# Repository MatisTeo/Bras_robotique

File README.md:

# 🤖 Projet Bras Robotique Contrôlé par Gant Connecté

## 🎥 Démonstration vidéo

## 📘 Présentation

Ce projet consiste à développer un **bras robotique à faible coût**, capable d'exécuter :
- des **mouvements automatiques prédéfinis**
- un **contrôle manuel à distance** à l'aide d’un **gant connecté**

L'objectif est de démontrer une alternative simple et économique pour la télémanipulation dans des environnements industriels.

## 🧠 Membres du projet
- **Téo Baillot d’Estivaux** — responsable software, modélisation 3D, banc de test
- **Matis Jaquet** — responsable hardware, PCB, assemblage électronique

## 🔧 Fonctionnalités
- Contrôle **automatique** via séquences programmées
- Contrôle **manuel en temps réel** via un gant avec capteur flex + MPU-6050
- Communication **sans fil via ESP-NOW (Wi-Fi)** entre gant et bras
- Structure imprimée en 3D, légère et modulaire
- Retour d’effort par détection de courant via INA219

## 📂 Contenu du dépôt
- `Hardware/` : Schémas et PCB sous KiCad
- `Software/` : Codes Arduino pour l’émetteur (gant) et le récepteur (bras)
- `Photos/Spécification/` : Images du montage
- `Memoire_Baillot_Jaquet.pdf` : Mémoire complet du projet (ELEC4 FISA 2024/2025)

## 🛠️ Composants utilisés
- 2x ESP32
- 1x MPU-6050 (accéléromètre)
- 1x capteur flex
- 5x servomoteurs SG90
- 1x INA219
- 1x bouton poussoir
- Câblage, breadboards, batteries

## 🚀 Instructions de montage
1. Imprimer les pièces 3D du bras
2. Souder les composants sur les PCB fournis
3. Assembler le gant en cousant les composants selon le schéma
4. Flasher les codes sur les ESP32 avec Arduino IDE
5. Alimenter les deux systèmes et tester les modes automatique et manuel

## 📎 Liens utiles
- [🔗 Dépôt GitHub](https://github.com/MatisTeo/Bras_robotique)
- [📄 Mémoire complet (PDF)](./Divers/Memoire_Baillot_Jaquet.pdf)

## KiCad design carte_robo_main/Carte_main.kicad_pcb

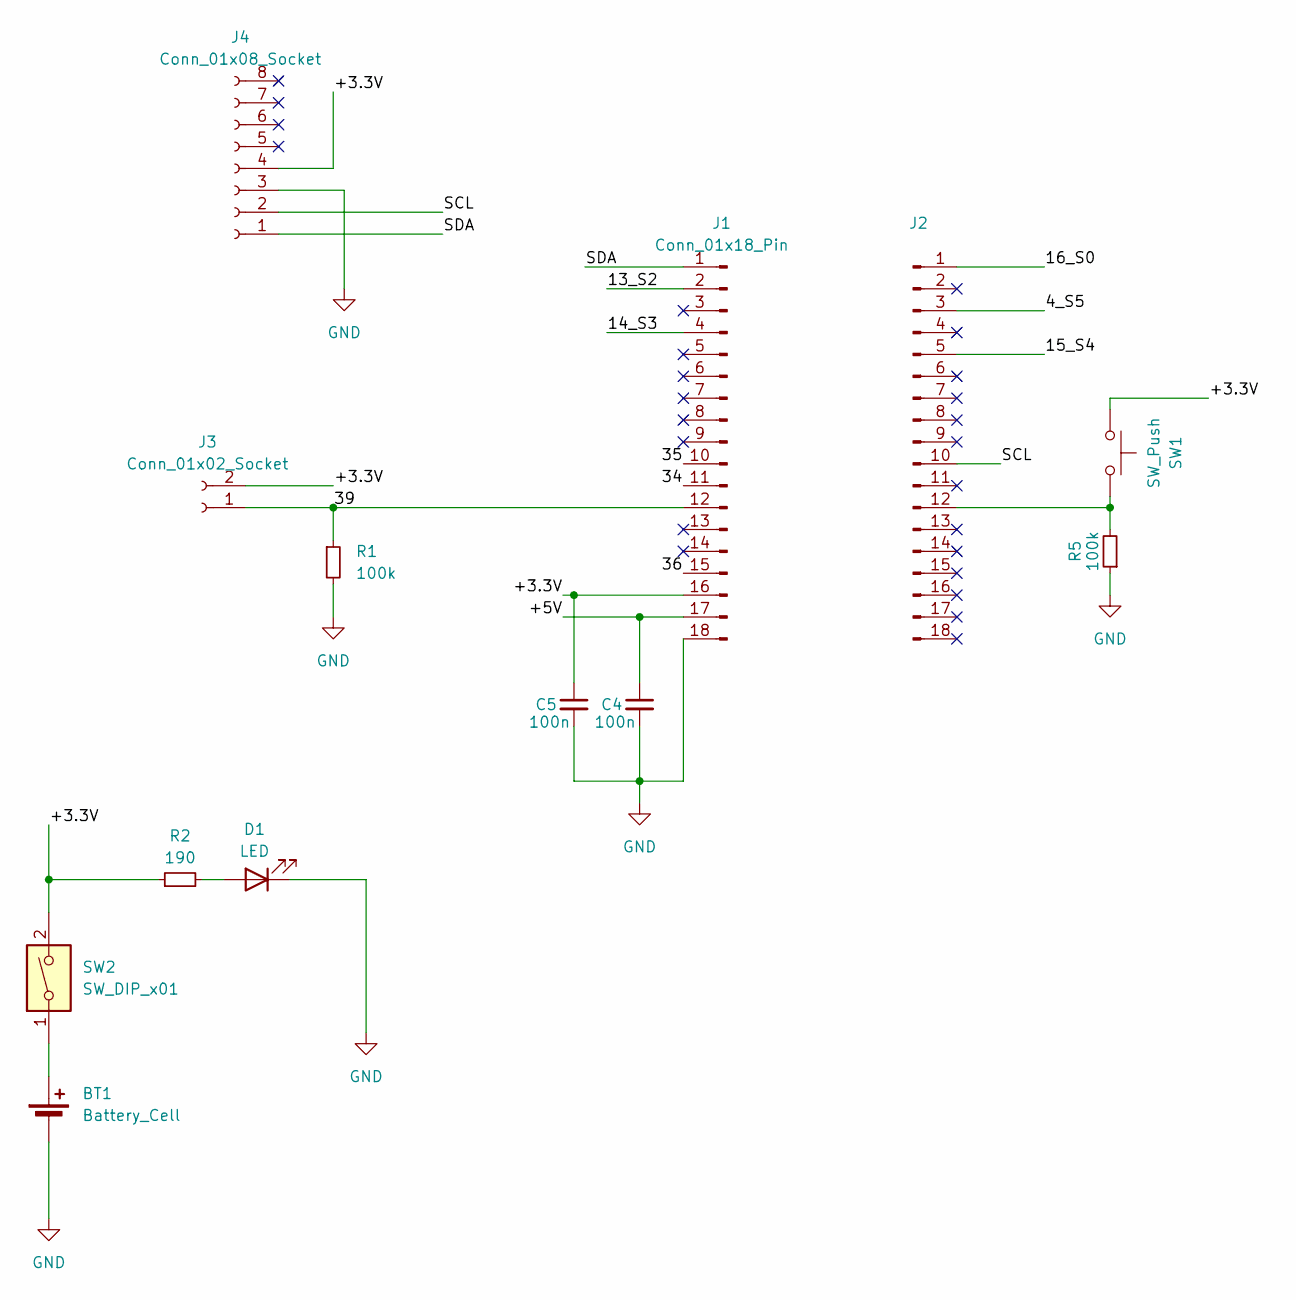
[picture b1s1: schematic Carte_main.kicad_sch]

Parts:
BT1: Battery_Cell; PinHeader_1x02_P2.54mm_Vertical
C4, C5: 100n; C_Disc_D4.3mm_W1.9mm_P5.00mm
D1: LED; LED_D3.0mm
J1, J2: Conn_01x18_Pin; PinHeader_1x18_P2.54mm_Vertical
J3: Conn_01x02_Socket; PinHeader_1x02_P2.54mm_Vertical
J4: Conn_01x08_Socket; PinHeader_1x08_P2.54mm_Vertical
R1, R5: 100k; R_Axial_DIN0207_L6.3mm_D2.5mm_P10.16mm_Horizontal
R2: 190; R_Axial_DIN0207_L6.3mm_D2.5mm_P10.16mm_Horizontal
SW1: SW_Push; SW_PUSH_6mm_H5mm
SW2: SW_DIP_x01; SW_slide-03_P5_THT

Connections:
/4_S5: J2.3
/13_S2: J1.2
/14_S3: J1.4
/15_S4: J2.5
/16_S0: J2.1
/34: J1.11
/35: J1.10
/36: J1.15
/39: J1.12, J3.1, R1.1
/+3.3V: C5.1, J1.16, J3.2, J4.4, R2.1, SW1.1, SW2.2
/+5V: C4.1, J1.17
/SCL: J2.10, J4.2
/SDA: J1.1, J4.1
GND: BT1.2 (-), C4.2, C5.2, D1.1 (K), J1.18, J4.3, R1.2, R5.1
unnamed: BT1.1 (+), SW2.1
unnamed: D1.2 (A), R2.2
unnamed: J2.12, R5.2, SW1.2

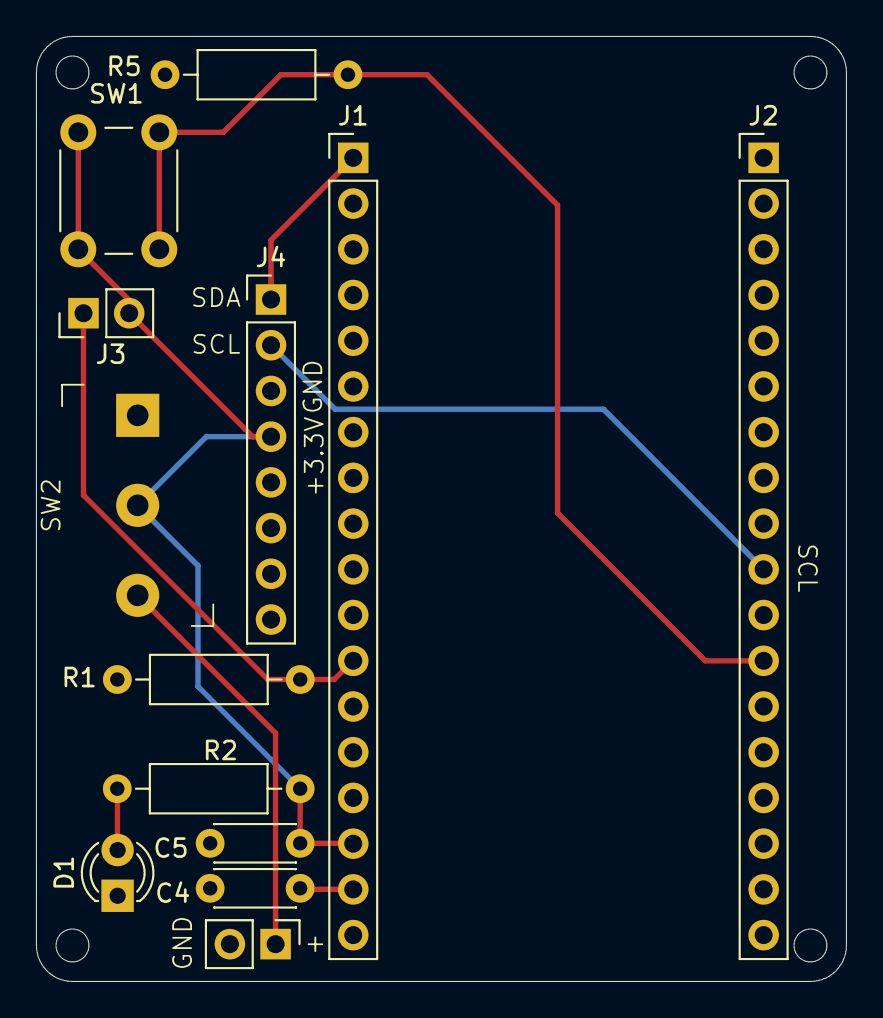
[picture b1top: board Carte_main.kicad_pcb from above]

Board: 2 copper layers, 45.0 x 52.5 mm, 13 parts (0 on the bottom side), 9 nets.

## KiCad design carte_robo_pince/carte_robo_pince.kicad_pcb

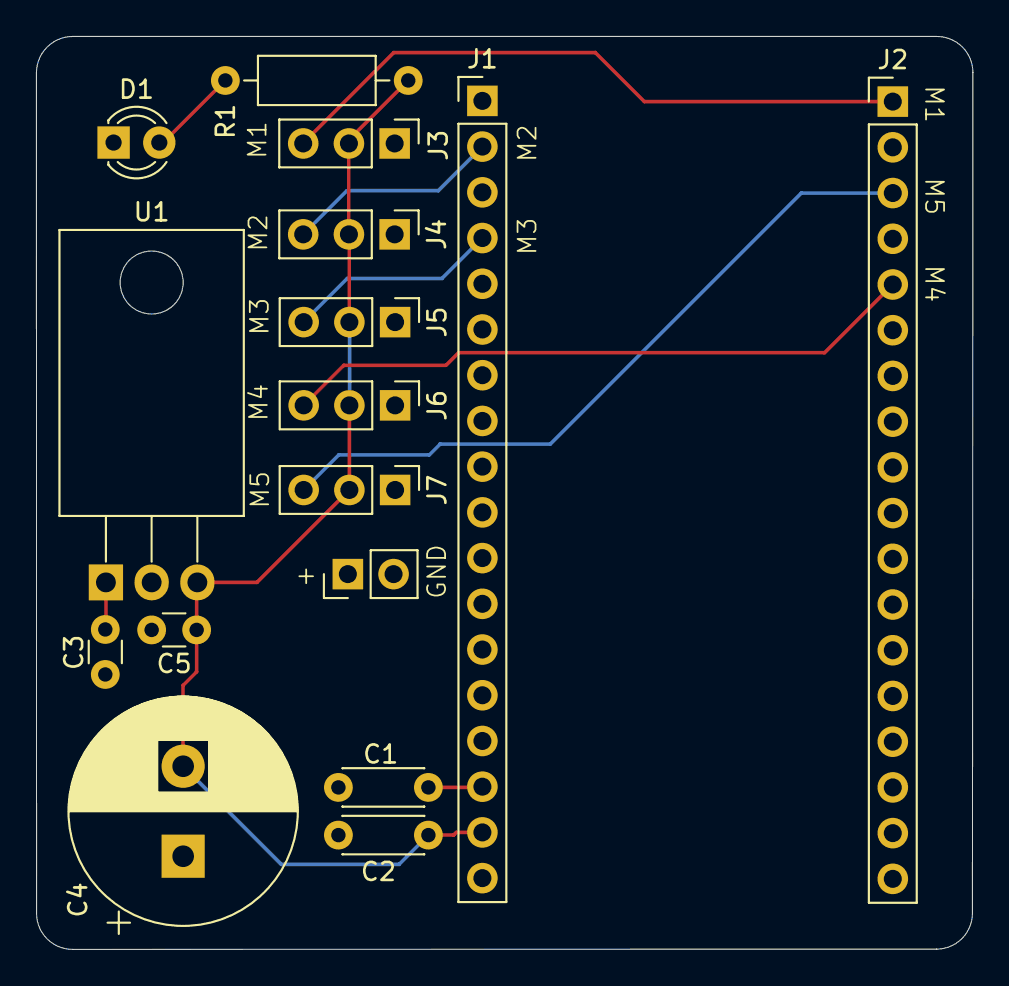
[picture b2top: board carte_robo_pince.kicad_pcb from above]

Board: 2 copper layers, 52.0 x 50.7 mm, 16 parts (0 on the bottom side), 10 nets.

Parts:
BT1: +8V; PinHeader_1x02_P2.54mm_Vertical
C1, C2: 100n; C_Disc_D4.3mm_W1.9mm_P5.00mm
C3: 0.33pF; C_Disc_D3.0mm_W1.6mm_P2.50mm
C4: 1000u; CP_Radial_D12.5mm_P5.00mm
C5: 0.1uF; C_Disc_D3.0mm_W1.6mm_P2.50mm
D1: LED; LED_D3.0mm
J1, J2: Conn_01x18_Pin; PinHeader_1x18_P2.54mm_Vertical
J3, J4, J5, J6, J7: Conn_01x03_Socket; PinHeader_1x03_P2.54mm_Vertical
R1: 330; R_Axial_DIN0207_L6.3mm_D2.5mm_P10.16mm_Horizontal
U1: KA78M05_TO252; TO-220-3_Horizontal_TabDown

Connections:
/4_S5: J2.3, J7.3
/13_S2: J1.2, J4.3
/14_S3: J1.4, J5.3
/15_S4: J2.5, J6.3
/16_S0: J2.1, J3.3
/+3.3V: C1.1, J1.16
/+5V: C2.1, C4.2, C5.1, J1.17, J3.2, J4.2, J5.2, J6.2, J7.2, R1.2, U1.3 (VO)
GND: BT1.2 (-), C1.2, C2.2, C3.2, C4.1, C5.2, D1.1 (K), J1.18, J3.1, J4.1, J5.1, J6.1, J7.1, U1.2 (GND)
unnamed: D1.2 (A), R1.1
unnamed: C3.1, U1.1 (VI)

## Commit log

2024-09-23 docs ajoutée
2024-11-28 compte rendu crée
2024-12-09 les deux rop merge
2024-12-14 14/12/2024
2025-01-07 pcb done
2025-02-06 last update
2025-03-02 version
2025-03-19 19/03
2025-04-01 01/04/25
2025-05-05 before copy branche matis to main
